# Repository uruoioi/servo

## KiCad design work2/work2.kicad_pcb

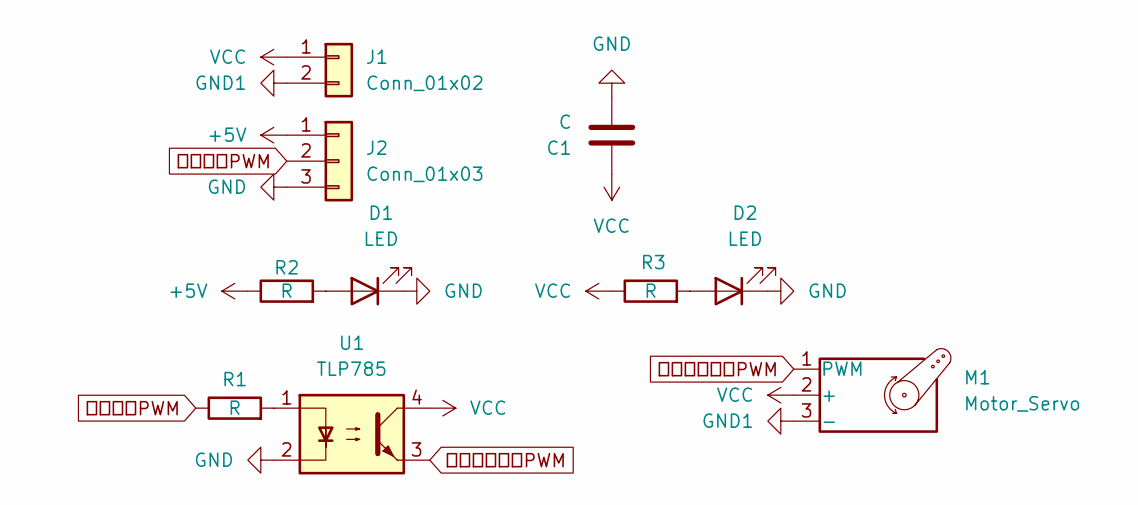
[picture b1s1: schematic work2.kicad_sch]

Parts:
C1: C; C_Disc_D3.0mm_W1.6mm_P2.50mm
D1, D2: LED; LED_D3.0mm
J1: Conn_01x02; JST_XA_S02B-XASK-1_1x02_P2.50mm_Horizontal
J2: Conn_01x03; JST_XA_S03B-XASK-1_1x03_P2.50mm_Horizontal
M1: Motor_Servo; PinHeader_1x03_P2.54mm_Vertical
R1, R2, R3: R; R_Axial_DIN0207_L6.3mm_D2.5mm_P10.16mm_Horizontal
U1: TLP785; DIP-4_W7.62mm

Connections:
+5V: J2.1, R2.1
GND: C1.2, D1.1 (K), D2.1 (K), J2.3, U1.2
GND1: J1.2, M1.3 (-)
unnamed: D1.2 (A), R2.2
unnamed: D2.2 (A), R3.2
unnamed: R1.2, U1.1
VCC: C1.1, J1.1, M1.2 (+), R3.1, U1.4
フォトカプラPWM: M1.1 (PWM), U1.3
マイコンPWM: J2.2, R1.1

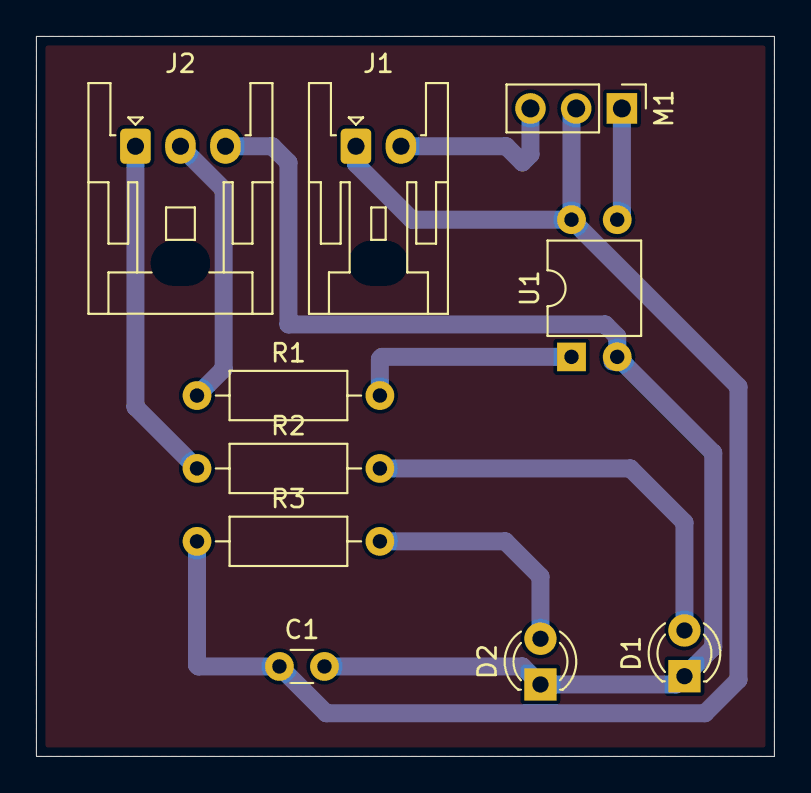
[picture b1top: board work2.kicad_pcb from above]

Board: 2 copper layers, 41.0 x 40.0 mm, 10 parts (0 on the bottom side), 9 nets.

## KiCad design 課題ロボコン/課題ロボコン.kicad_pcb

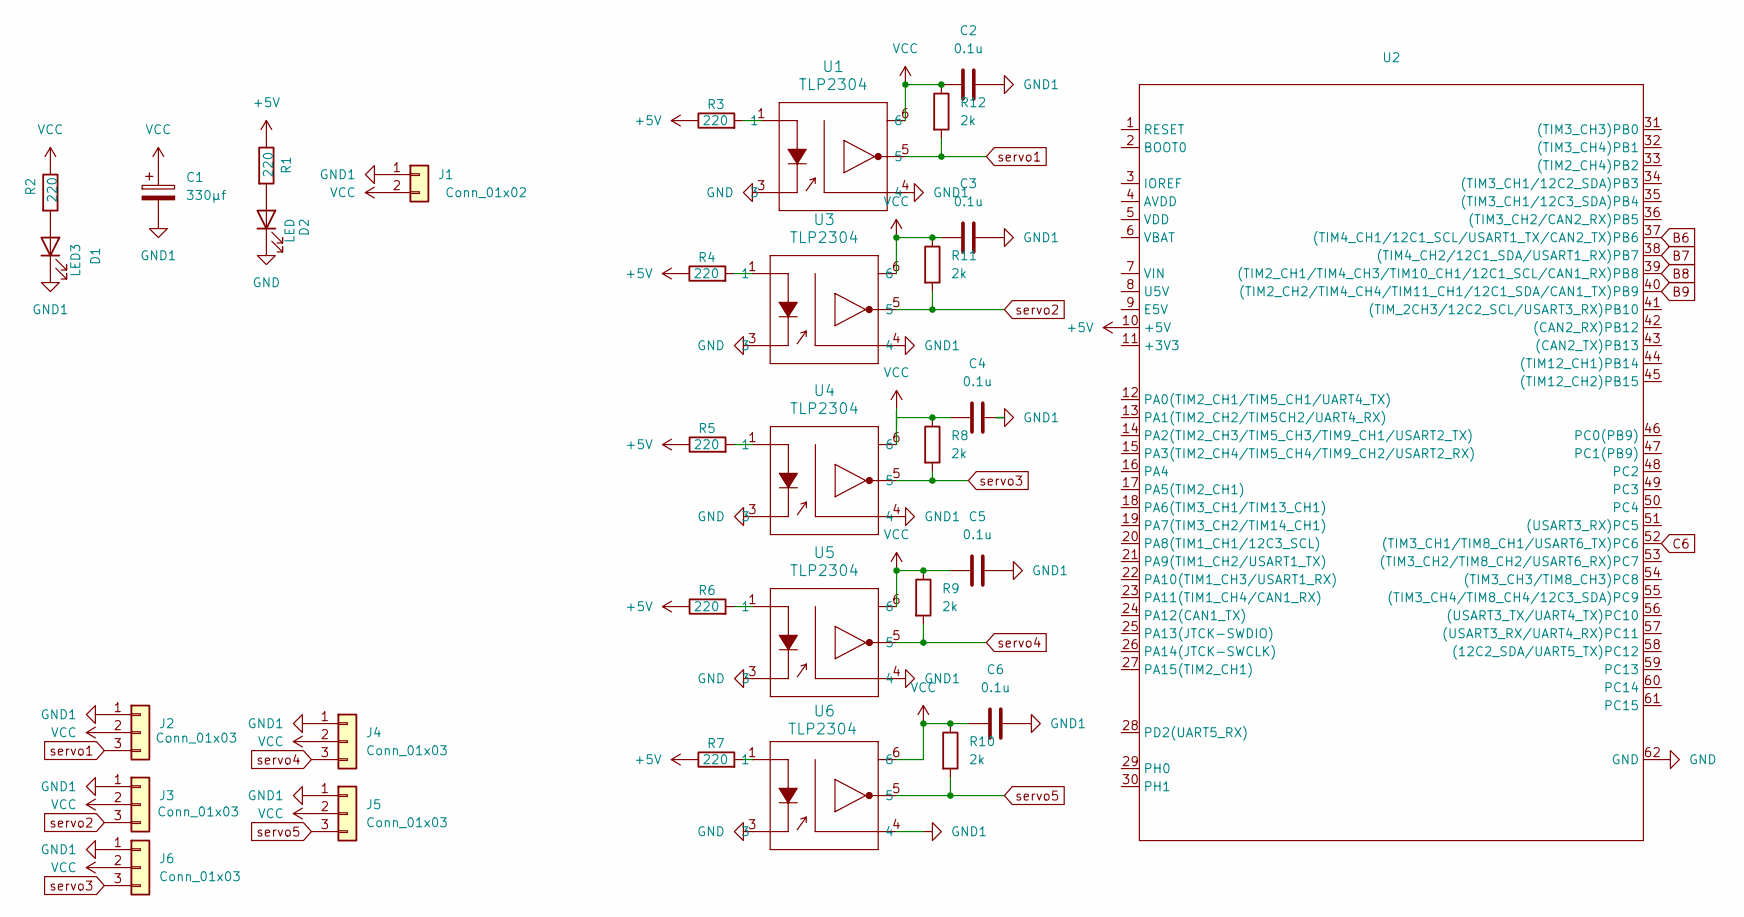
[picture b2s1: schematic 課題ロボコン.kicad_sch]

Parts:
C1: 330μf; CP_Radial_D5.0mm_P2.00mm
C2, C3, C4, C5, C6: 0.1u; C_Disc_D3.0mm_W1.6mm_P2.50mm
D1: LED3; LED_D3.0mm
D2: LED; LED_D3.0mm
J1: Conn_01x02; AMASS_XT60PW-M_1x02_P7.20mm_Horizontal
J2, J3, J4, J5, J6: Conn_01x03; PinHeader_1x03_P2.54mm_Vertical
R1, R2, R3, R4, R5, R6, R7: 220; R_Axial_DIN0207_L6.3mm_D2.5mm_P10.16mm_Horizontal
R8, R9, R10, R11, R12: 2k; R_Axial_DIN0207_L6.3mm_D2.5mm_P10.16mm_Horizontal
U1, U3, U4, U5, U6: TLP2304; 5pin SO6_TOS
U2: STM32F446RE_Nucleo

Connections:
+5V: R1.1, R3.1, R4.1, R5.1, R6.1, R7.1, U2.10 (+5V)
B6: U2.37 ((TIM4_CH1/12C1_SCL/USART1_TX/CAN2_TX)PB6)
B7: U2.38 ((TIM4_CH2/12C1_SDA/USART1_RX)PB7)
B8: U2.39 ((TIM2_CH1/TIM4_CH3/TIM10_CH1/12C1_SCL/C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)
B9: U2.40 ((TIM2_CH2/TIM4_CH4/TIM11_CH1/12C1_SDA/C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)
C6: U2.52 ((TIM3_CH1/TIM8_CH1/USART6_TX)PC6)
GND: D2.1 (K), U1.3, U2.62 (GND), U3.3, U4.3, U5.3, U6.3
GND1: C1.2, C2.2, C3.2, C4.2, C5.2, C6.2, D1.1 (K), J1.1, J2.1, J3.1, J4.1, J5.1, J6.1, U1.4, U3.4, U4.4, U5.4, U6.4
unnamed: C4.1, R8.1
unnamed: D1.2 (A), R2.2
unnamed: D2.2 (A), R1.2
unnamed: R3.2, U1.1
unnamed: R4.2, U3.1
unnamed: R5.2, U4.1
unnamed: R6.2, U5.1
unnamed: R7.2, U6.1
VCC: C1.1, C2.1, C3.1, C5.1, C6.1, J1.2, J2.2, J3.2, J4.2, J5.2, J6.2, R2.1, R9.1, R10.1, R11.1, R12.1, U1.6, U3.6, U4.6, U5.6, U6.6
servo1: J2.3, R12.2, U1.5
servo2: J3.3, R11.2, U3.5
servo3: J6.3, R8.2, U4.5
servo4: J4.3, R9.2, U5.5
servo5: J5.3, R10.2, U6.5

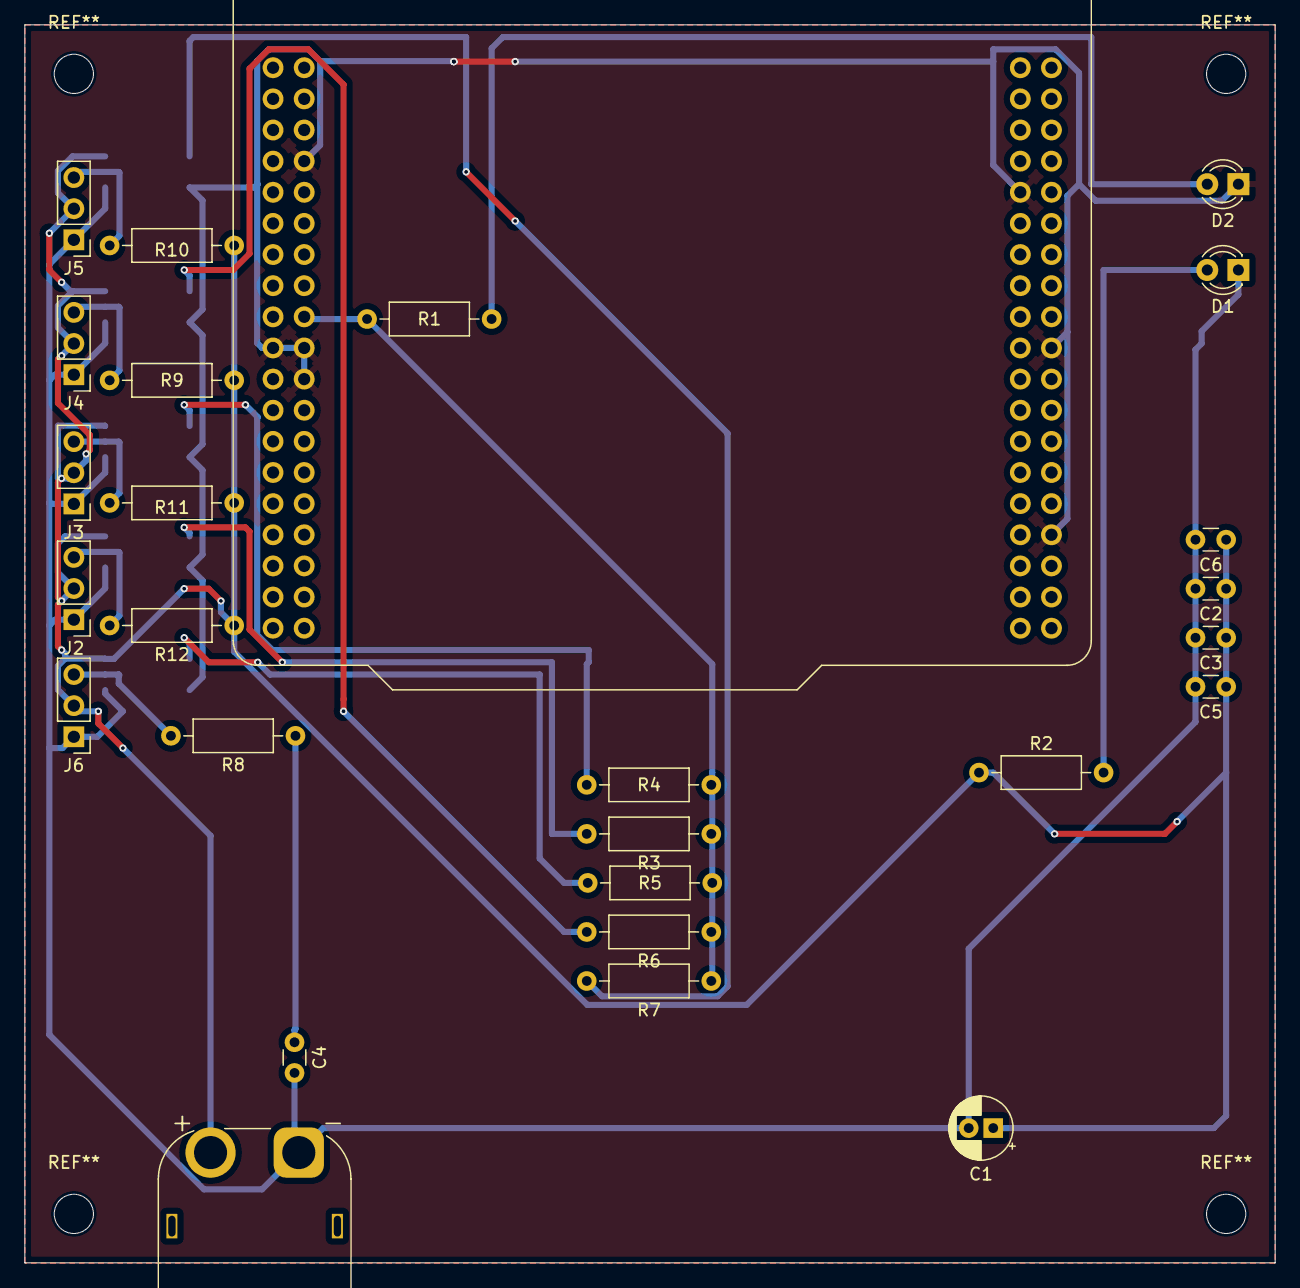
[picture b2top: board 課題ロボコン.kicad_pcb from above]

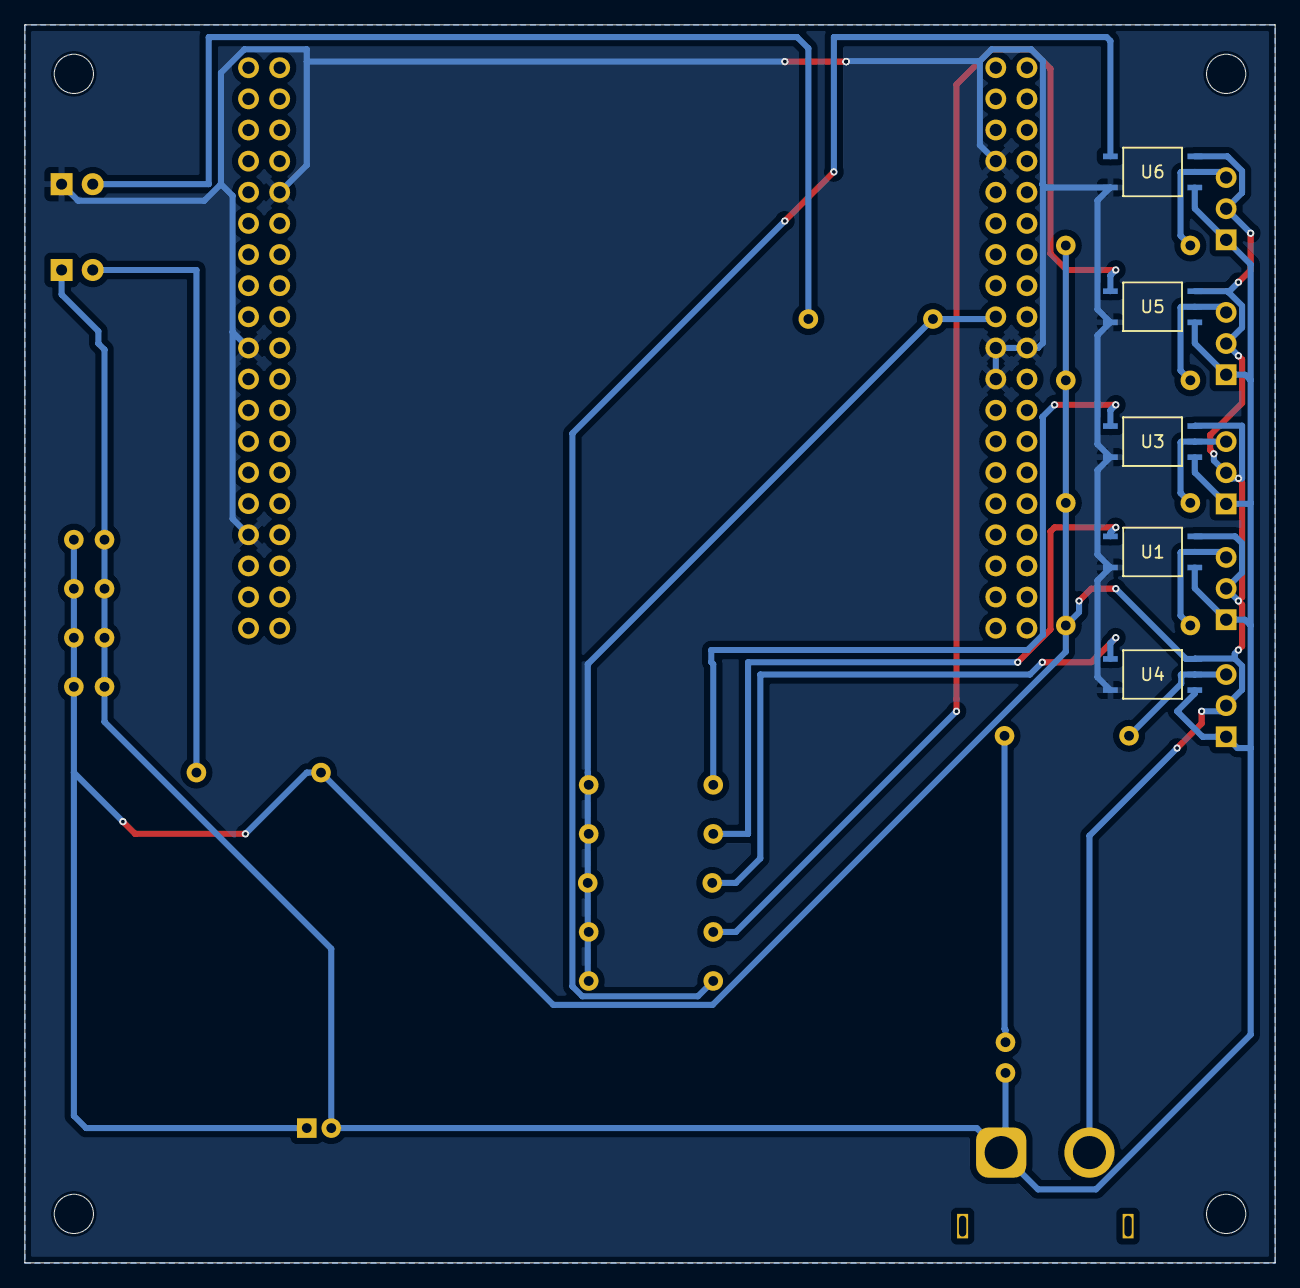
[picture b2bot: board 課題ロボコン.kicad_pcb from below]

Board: 2 copper layers, 102.0 x 101.0 mm, 32 parts (5 on the bottom side), 17 nets.
